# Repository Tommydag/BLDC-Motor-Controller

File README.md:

# BLDC-Motor-Controller
A BLDC Motor Controller for small electric vehicles

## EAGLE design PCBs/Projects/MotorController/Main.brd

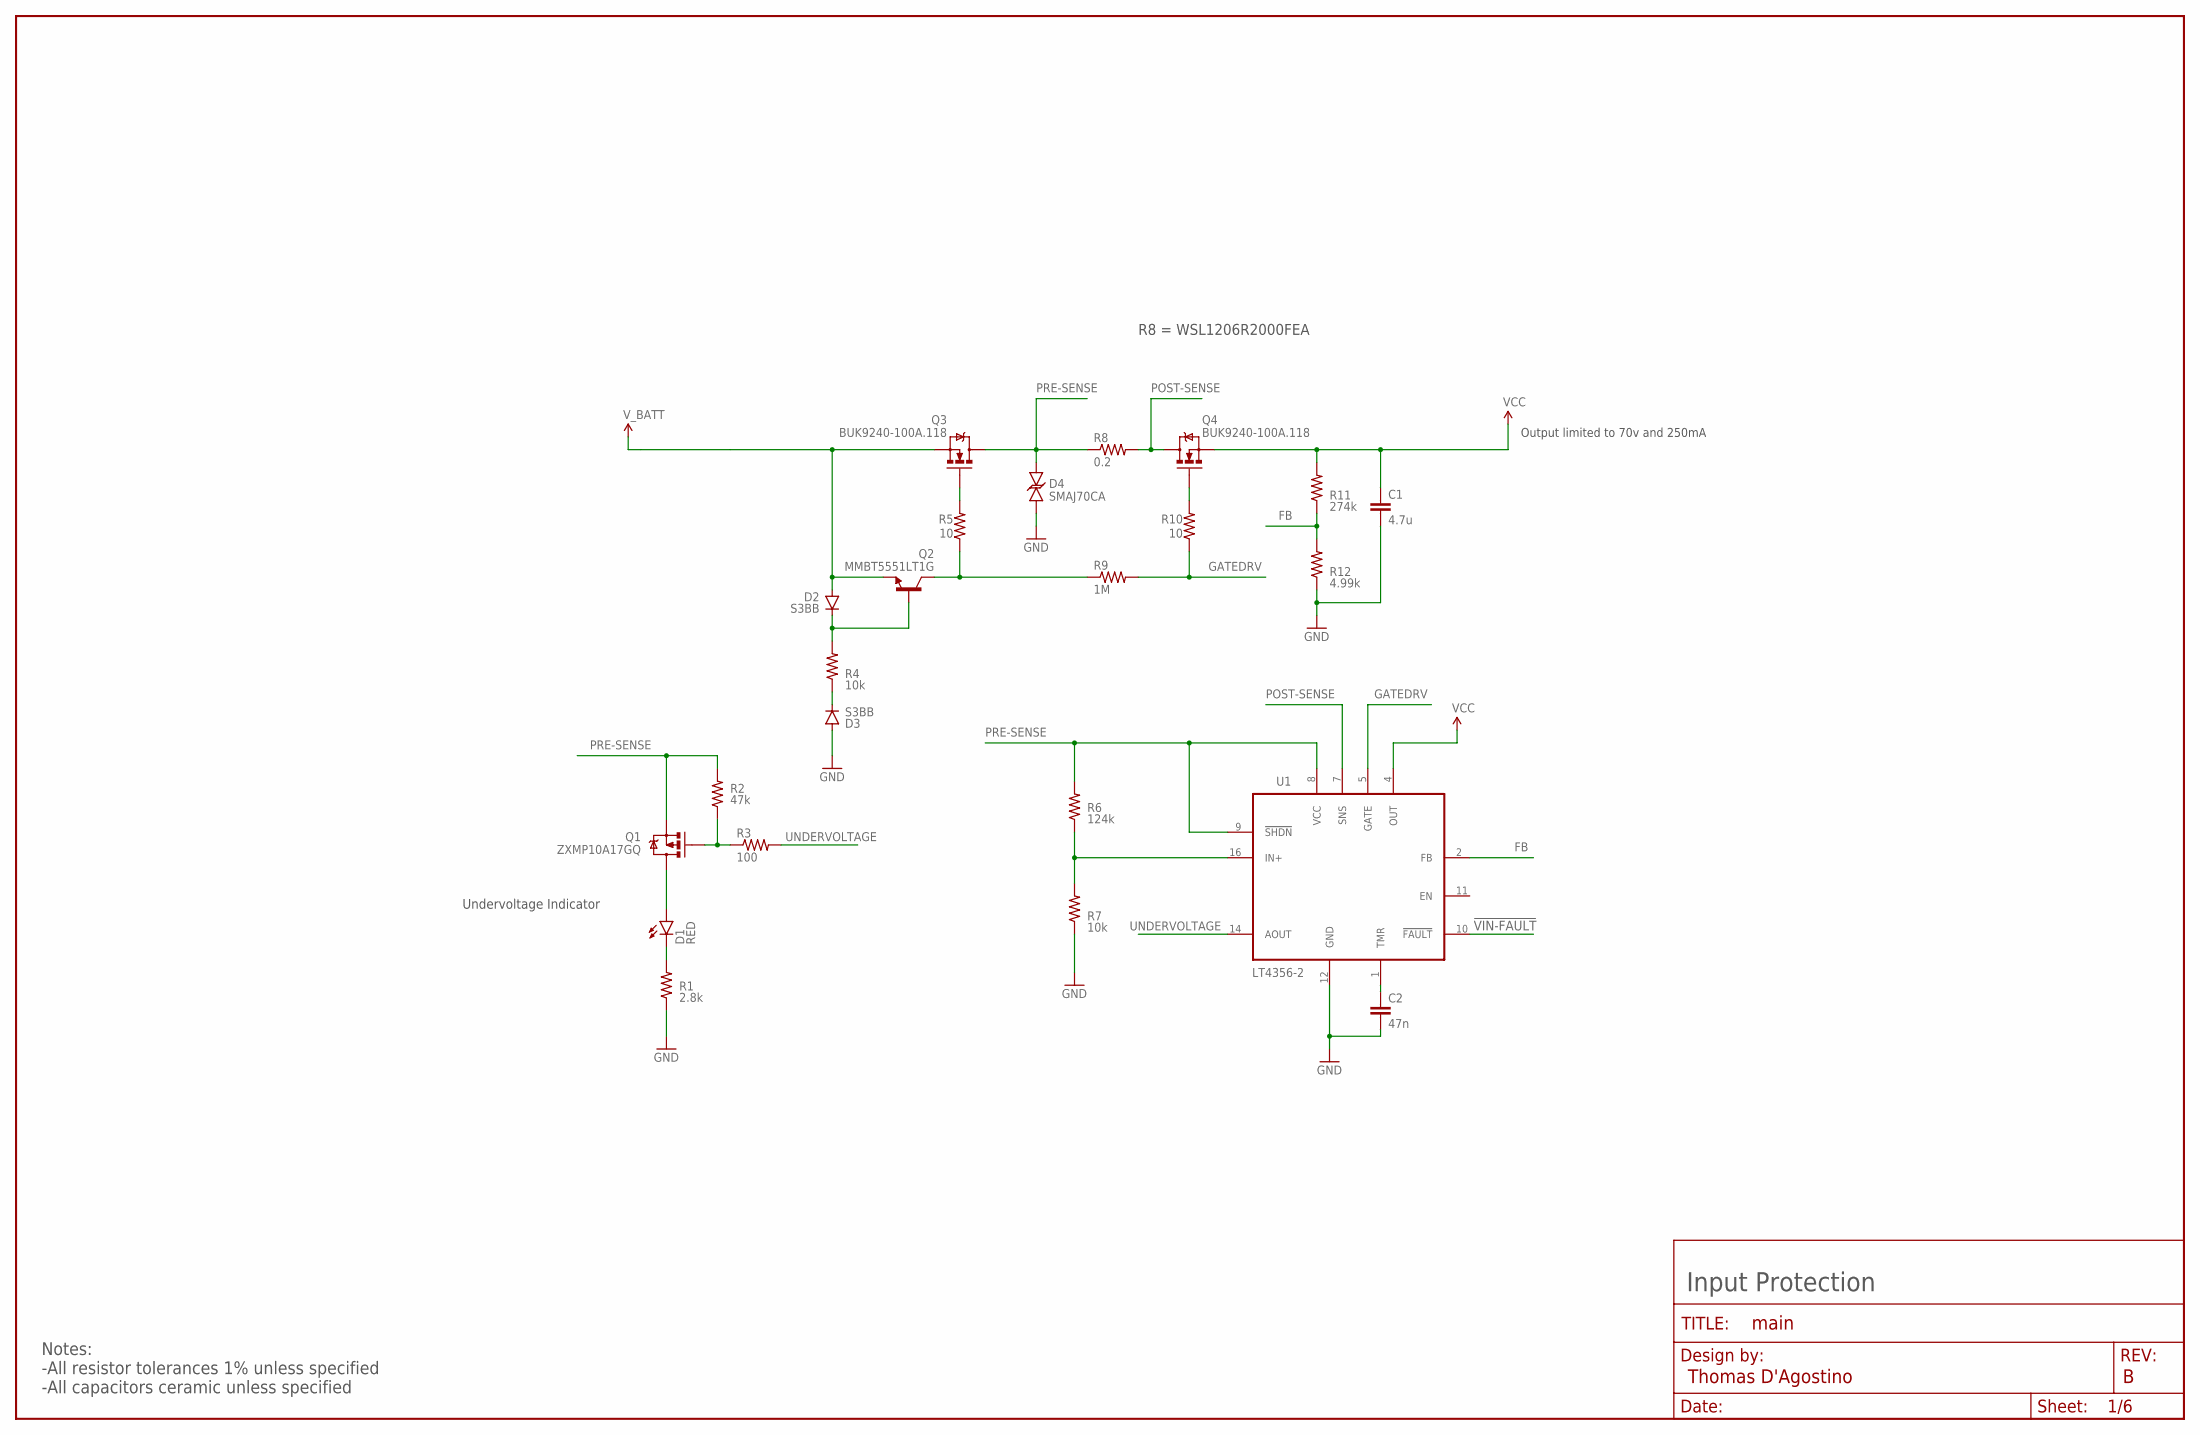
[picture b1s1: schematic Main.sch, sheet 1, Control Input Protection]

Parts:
C1: 4.7u; 1210
C2: 47n; 0805
D1: RED; LED-1206
D2, D3: S3BB; SMB-DIODE
D4: SMAJ70CA; SMA-DIODE-BI
FRAME1: FRAME-LEDGER; CREATIVE_COMMONS
Q1: ZXMP10A17GQ; SOT223
Q2: MMBT5551LT1G; SOT23-3
Q3, Q4: BUK9240-100A.118; DPAK
R1: 2.8k; 1206
R2: 47k; 0805
R3: 100; 0805
R4, R7: 10k; 0805
R5, R10: 10; 0805
R6: 124k; 0805
R8: 0.2; 1206
R9: 1M; 0805
R11: 274k; 0805
R12: 4.99k; 0805
U1: LT4356-2; SOIC-16

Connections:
!VIN-FAULT: U1.10 (!FAULT); also elsewhere on the board
FB: R11.1, R12.2, U1.2 (FB)
GATEDRV: R9.2, R10.1, U1.5 (GATE)
GND: C1.2, C2.2, D3.A, D4.A, R1.1, R7.1, R12.1, U1.12 (GND); also elsewhere on the board
unnamed: C2.1, U1.1 (TMR)
unnamed: D1.C, R1.2
unnamed: Q3.1 (G), R5.2
unnamed: D2.C, Q2.1 (B), R4.2
unnamed: Q4.1 (G), R10.2
unnamed: R6.1, R7.2, U1.16 (IN+)
unnamed: Q1.1 (G), R2.1, R3.1
unnamed: Q2.3 (C), R5.1, R9.1
unnamed: D1.A, Q1.2 (D), Q1.4 (D)
unnamed: D3.C, R4.1
POST-SENSE: Q4.4 (D), R8.2, U1.7 (SNS)
PRE-SENSE: D4.C, Q1.3 (S), Q3.4 (D), R2.2, R6.2, R8.1, U1.8 (VCC), U1.9 (!SHDN)
UNDERVOLTAGE: R3.2, U1.14 (AOUT)
VCC: C1.1, Q4.3 (S), R11.2, U1.4 (OUT); also elsewhere on the board
V_BATT: D2.A, Q2.2 (E), Q3.3 (S); also elsewhere on the board

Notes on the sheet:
Output limited to 70v and 250mA
Undervoltage Indicator
Input Protection
Notes: -All resistor tolerances 1% unless specified -All capacitors ceramic unless specified
R8 = WSL1206R2000FEA

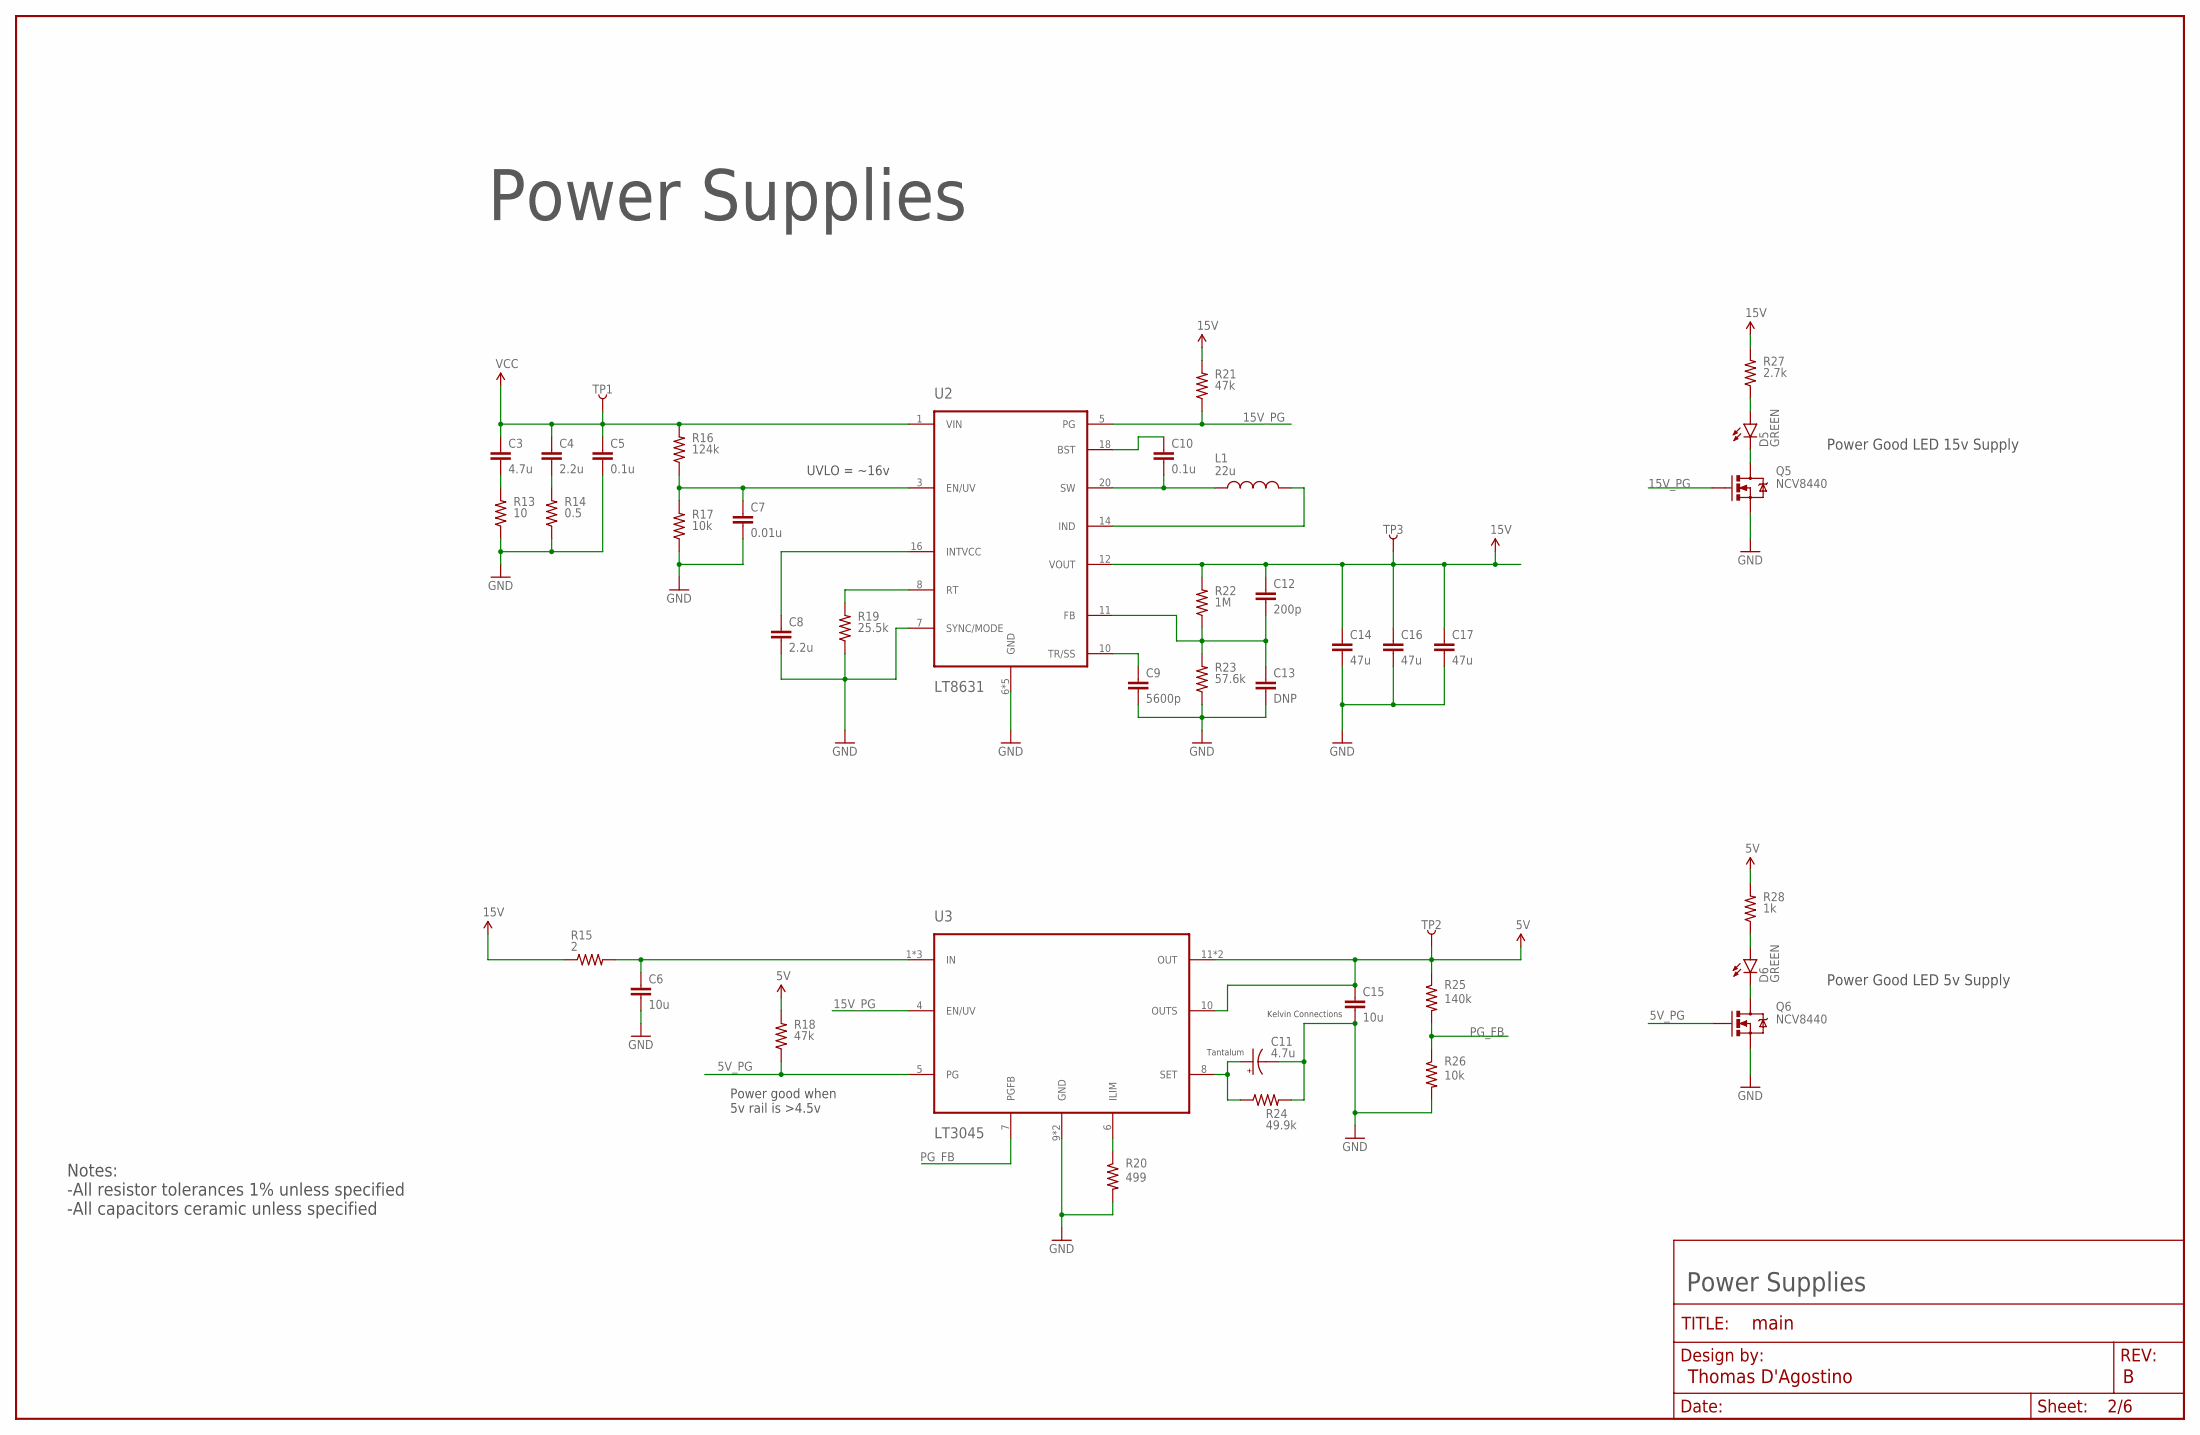
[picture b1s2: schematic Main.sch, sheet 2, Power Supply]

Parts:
C3: 4.7u; 1210
C4: 2.2u; 1210
C5, C10: 0.1u; 0805
C6, C15: 10u; 1210
C7: 0.01u; 0805
C8: 2.2u; 0805
C9: 5600p; 0805
C11: 4.7u; EIA3216
C12: 200p; 0805
C13: DNP; 0805
C14, C16, C17: 47u; 1210
D5, D6: GREEN; LED-1206
FRAME2: FRAME-LEDGER; CREATIVE_COMMONS
L1: 22u; IND_SMD_SRP7050TA
Q5, Q6: NCV8440; SOT223
R13: 10; 0805
R14: 0.5; 0805
R15: 2; 1206
R16: 124k; 0805
R17, R26: 10k; 0805
R18, R21: 47k; 0805
R19: 25.5k; 0805
R20: 499; 0805
R22: 1M; 0805
R23: 57.6k; 0805
R24: 49.9k; 0805
R25: 140k; 0805
R27: 2.7k; 0805
R28: 1k; 0805
TP1, TP2, TP3: TEST-POINTRCT-0C; TEST-POINT-MINI
U2: LT8631; TSSOP-20-FE
U3: LT3045; MSOP-12-EP

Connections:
5V: C15.1, R18.2, R25.1, R28.2, TP2.P$1, U3.10 (OUTS), U3.11 (OUT), U3.12 (OUT); also elsewhere on the board
5V_PG: Q6.1 (G), R18.1, U3.5 (PG)
5V_SET_CONNECTION: C11.A (+), R24.1, U3.8 (SET)
15V: C12.1, C14.1, C16.1, C17.1, R15.1, R21.2, R22.2, R27.2, TP3.P$1, U2.12 (VOUT); also elsewhere on the board
15V_PG: Q5.1 (G), R21.1, U2.5 (PG), U3.4 (EN/UV)
GND: C5.2, C6.2, C7.2, C8.2, C9.2, C11.C (-), C13.2, C14.2, C15.2, C16.2, C17.2, Q5.3 (S), Q6.3 (S), R13.1, R14.1, R17.1, R19.1, R20.2, R23.1, R24.2, R26.2, U2.6 (GND), U2.7 (SYNC/MODE), U2.9 (GND), U2.13 (GND), U2.15 (GND), U2.EXP (GND), U3.9 (GND), U3.EXP (GND); also elsewhere on the board
ILIMIT_5V: R20.1, U3.6 (ILIM)
unnamed: C10.2, L1.P$1 (1), U2.20 (SW)
unnamed: L1.P$2 (2), U2.14 (IND)
unnamed: C10.1, U2.18 (BST)
unnamed: C7.1, R16.1, R17.2, U2.3 (EN/UV)
unnamed: C8.1, U2.16 (INTVCC)
unnamed: R19.2, U2.8 (RT)
unnamed: C9.1, U2.10 (TR/SS)
unnamed: C12.2, C13.1, R22.1, R23.2, U2.11 (FB)
unnamed: C6.1, R15.2, U3.1 (IN), U3.2 (IN), U3.3 (IN)
unnamed: C3.2, R13.2
unnamed: C4.2, R14.2
unnamed: D5.C, Q5.2 (D), Q5.4 (D)
unnamed: D5.A, R27.1
unnamed: D6.A, R28.1
unnamed: D6.C, Q6.2 (D), Q6.4 (D)
PG_FB: R25.2, R26.1, U3.7 (PGFB)
VCC: C3.1, C4.1, C5.1, R16.2, TP1.P$1, U2.1 (VIN); also elsewhere on the board

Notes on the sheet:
Power Supplies
Notes: -All resistor tolerances 1% unless specified -All capacitors ceramic unless specified
UVLO = ~16v
Kelvin Connections
Power good when 5v rail is >4.5v
Tantalum
Power Good LED 15v Supply
Power Good LED 5v Supply

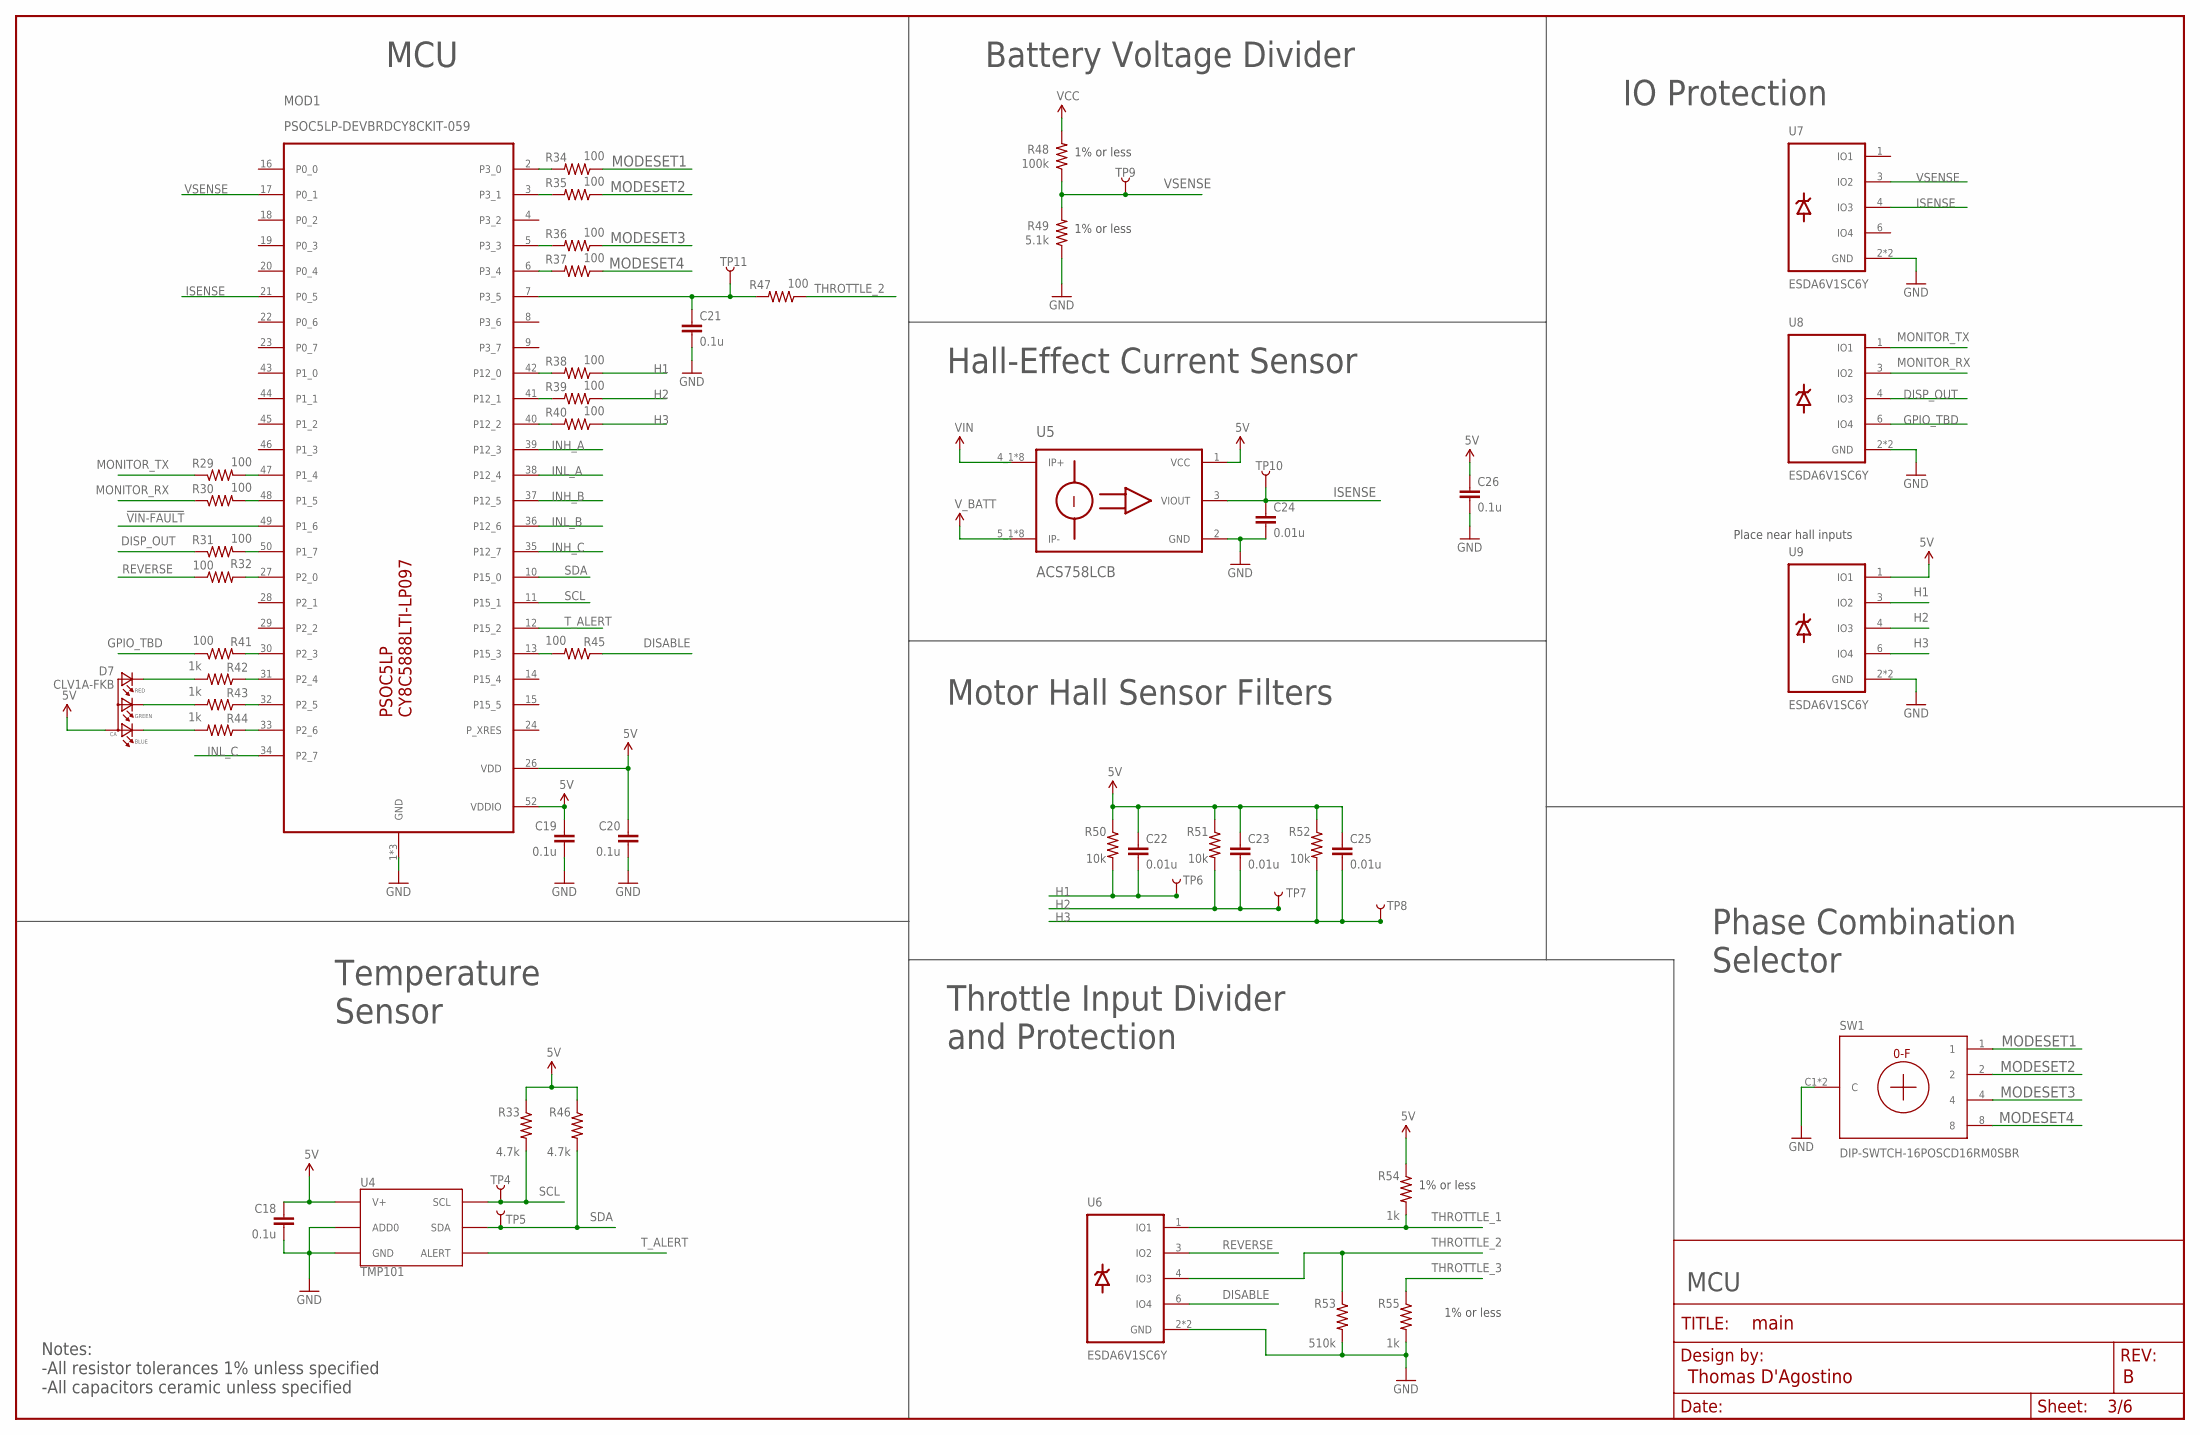
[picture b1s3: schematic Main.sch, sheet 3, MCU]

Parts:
C18, C19, C20, C21, C26: 0.1u; 0805
C22, C23, C24, C25: 0.01u; 0805
D7: CLV1A-FKB; P-LCC-4-3
FRAME3: FRAME-LEDGER; CREATIVE_COMMONS
MOD1: PSOC5LP-DEVBRDCY8CKIT-059; CYKIT059
R29, R30, R31, R32, R34, R35, R36, R37, R38, R39, R40, R41, R45, R47: 100; 0805
R33, R46: 4.7k; 0805
R42, R43, R44, R54, R55: 1k; 0805
R48: 100k; 1206
R49: 5.1k; 1206
R50, R51, R52: 10k; 0805
R53: 510k; 0805
SW1: DIP-SWTCH-16POSCD16RM0SBR; DIP-8MM
TP4, TP5, TP6, TP7, TP8, TP9, TP10, TP11: TEST-POINTRCT-0C; TEST-POINT-MINI
U4: TMP101; SOT23-6
U5: ACS758LCB; CB5PIN
U6, U7, U8, U9: ESDA6V1SC6Y; SOT23-6

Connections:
5V: C18.1, C19.1, C20.1, C22.1, C23.1, C25.1, C26.1, D7.2 (ANODE), MOD1.26 (VDD), MOD1.52 (VDDIO), R33.1, R46.1, R50.1, R51.1, R52.1, R54.1, U4.4 (V+), U5.1 (VCC), U9.1 (IO1); also elsewhere on the board
!VIN-FAULT: MOD1.49 (P1_6); also elsewhere on the board
DISABLE: R45.1, U6.6 (IO4); also elsewhere on the board
DISP_OUT: R31.1, U8.6 (IO4); also elsewhere on the board
GND: C18.2, C19.2, C20.2, C21.2, C24.2, C26.2, MOD1.1 (GND), MOD1.25 (GND), MOD1.51 (GND), R49.1, R53.2, R55.2, SW1.C1 (C), SW1.C2 (C), U4.2 (GND), U4.5 (ADD0), U5.2 (GND), U6.2 (GND), U6.5 (GND), U7.2 (GND), U7.5 (GND), U8.2 (GND), U8.5 (GND), U9.2 (GND), U9.5 (GND); also elsewhere on the board
GPIO_TBD: R41.1, U8.4 (IO3); also elsewhere on the board
H1: C22.2, R38.1, R50.2, TP6.P$1, U9.3 (IO2); also elsewhere on the board
H2: C23.2, R39.1, R51.2, TP7.P$1, U9.4 (IO3); also elsewhere on the board
H3: C25.2, R40.1, R52.2, TP8.P$1, U9.6 (IO4); also elsewhere on the board
INH_A: MOD1.39 (P12_3); also elsewhere on the board
INH_B: MOD1.37 (P12_5); also elsewhere on the board
INH_C: MOD1.35 (P12_7); also elsewhere on the board
INL_A: MOD1.38 (P12_4); also elsewhere on the board
INL_B: MOD1.36 (P12_6); also elsewhere on the board
INL_C: MOD1.34 (P2_7); also elsewhere on the board
ISENSE: C24.1, MOD1.21 (P0_5), TP10.P$1, U5.3 (VIOUT), U7.4 (IO3)
MODESET1: R34.1, SW1.1
MODESET2: R35.1, SW1.2
MODESET3: R36.1, SW1.4
MODESET4: R37.1, SW1.8
MONITOR_RX: R30.1, U8.1 (IO1); also elsewhere on the board
MONITOR_TX: R29.1, U8.3 (IO2); also elsewhere on the board
unnamed: MOD1.42 (P12_0), R38.2
unnamed: MOD1.13 (P15_3), R45.2
unnamed: MOD1.5 (P3_3), R36.2
unnamed: MOD1.33 (P2_6), R44.1
unnamed: MOD1.32 (P2_5), R43.1
unnamed: MOD1.31 (P2_4), R42.1
unnamed: D7.3 (BLUE), R44.2
unnamed: D7.4 (GREEN), R43.2
unnamed: D7.1 (RED), R42.2
unnamed: C21.1, MOD1.7 (P3_5), R47.2, TP11.P$1
unnamed: MOD1.50 (P1_7), R31.2
unnamed: MOD1.30 (P2_3), R41.2
unnamed: MOD1.47 (P1_4), R29.2
unnamed: MOD1.48 (P1_5), R30.2
unnamed: MOD1.41 (P12_1), R39.2
unnamed: MOD1.40 (P12_2), R40.2
unnamed: MOD1.27 (P2_0), R32.2
unnamed: MOD1.3 (P3_1), R35.2
unnamed: MOD1.2 (P3_0), R34.2
unnamed: MOD1.6 (P3_4), R37.2
REVERSE: R32.1, U6.3 (IO2); also elsewhere on the board
SCL: MOD1.11 (P15_1), R33.2, TP4.P$1, U4.1 (SCL)
SDA: MOD1.10 (P15_0), R46.2, TP5.P$1, U4.6 (SDA)
THROTTLE_1: R54.2, U6.1 (IO1); also elsewhere on the board
THROTTLE_2: R47.1, R53.1, U6.4 (IO3); also elsewhere on the board
THROTTLE_3: R55.1; also elsewhere on the board
T_ALERT: MOD1.12 (P15_2), U4.3 (ALERT)
VCC: R48.2; also elsewhere on the board
VIN: U5.4_1 (IP+), U5.4_2 (IP+), U5.4_3 (IP+), U5.4_4 (IP+), U5.4_5 (IP+), U5.4_6 (IP+), U5.4_7 (IP+), U5.4_8 (IP+); also elsewhere on the board
VSENSE: MOD1.17 (P0_1), R48.1, R49.2, TP9.P$1, U7.3 (IO2)
V_BATT: U5.5_1 (IP-), U5.5_2 (IP-), U5.5_3 (IP-), U5.5_4 (IP-), U5.5_5 (IP-), U5.5_6 (IP-), U5.5_7 (IP-), U5.5_8 (IP-); also elsewhere on the board

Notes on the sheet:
Place near hall inputs
1% or less
MCU
Temperature Sensor
Battery Voltage Divider
Hall-Effect Current Sensor
Motor Hall Sensor Filters
Throttle Input Divider and Protection
IO Protection
Notes: -All resistor tolerances 1% unless specified -All capacitors ceramic unless specified
Phase Combination Selector

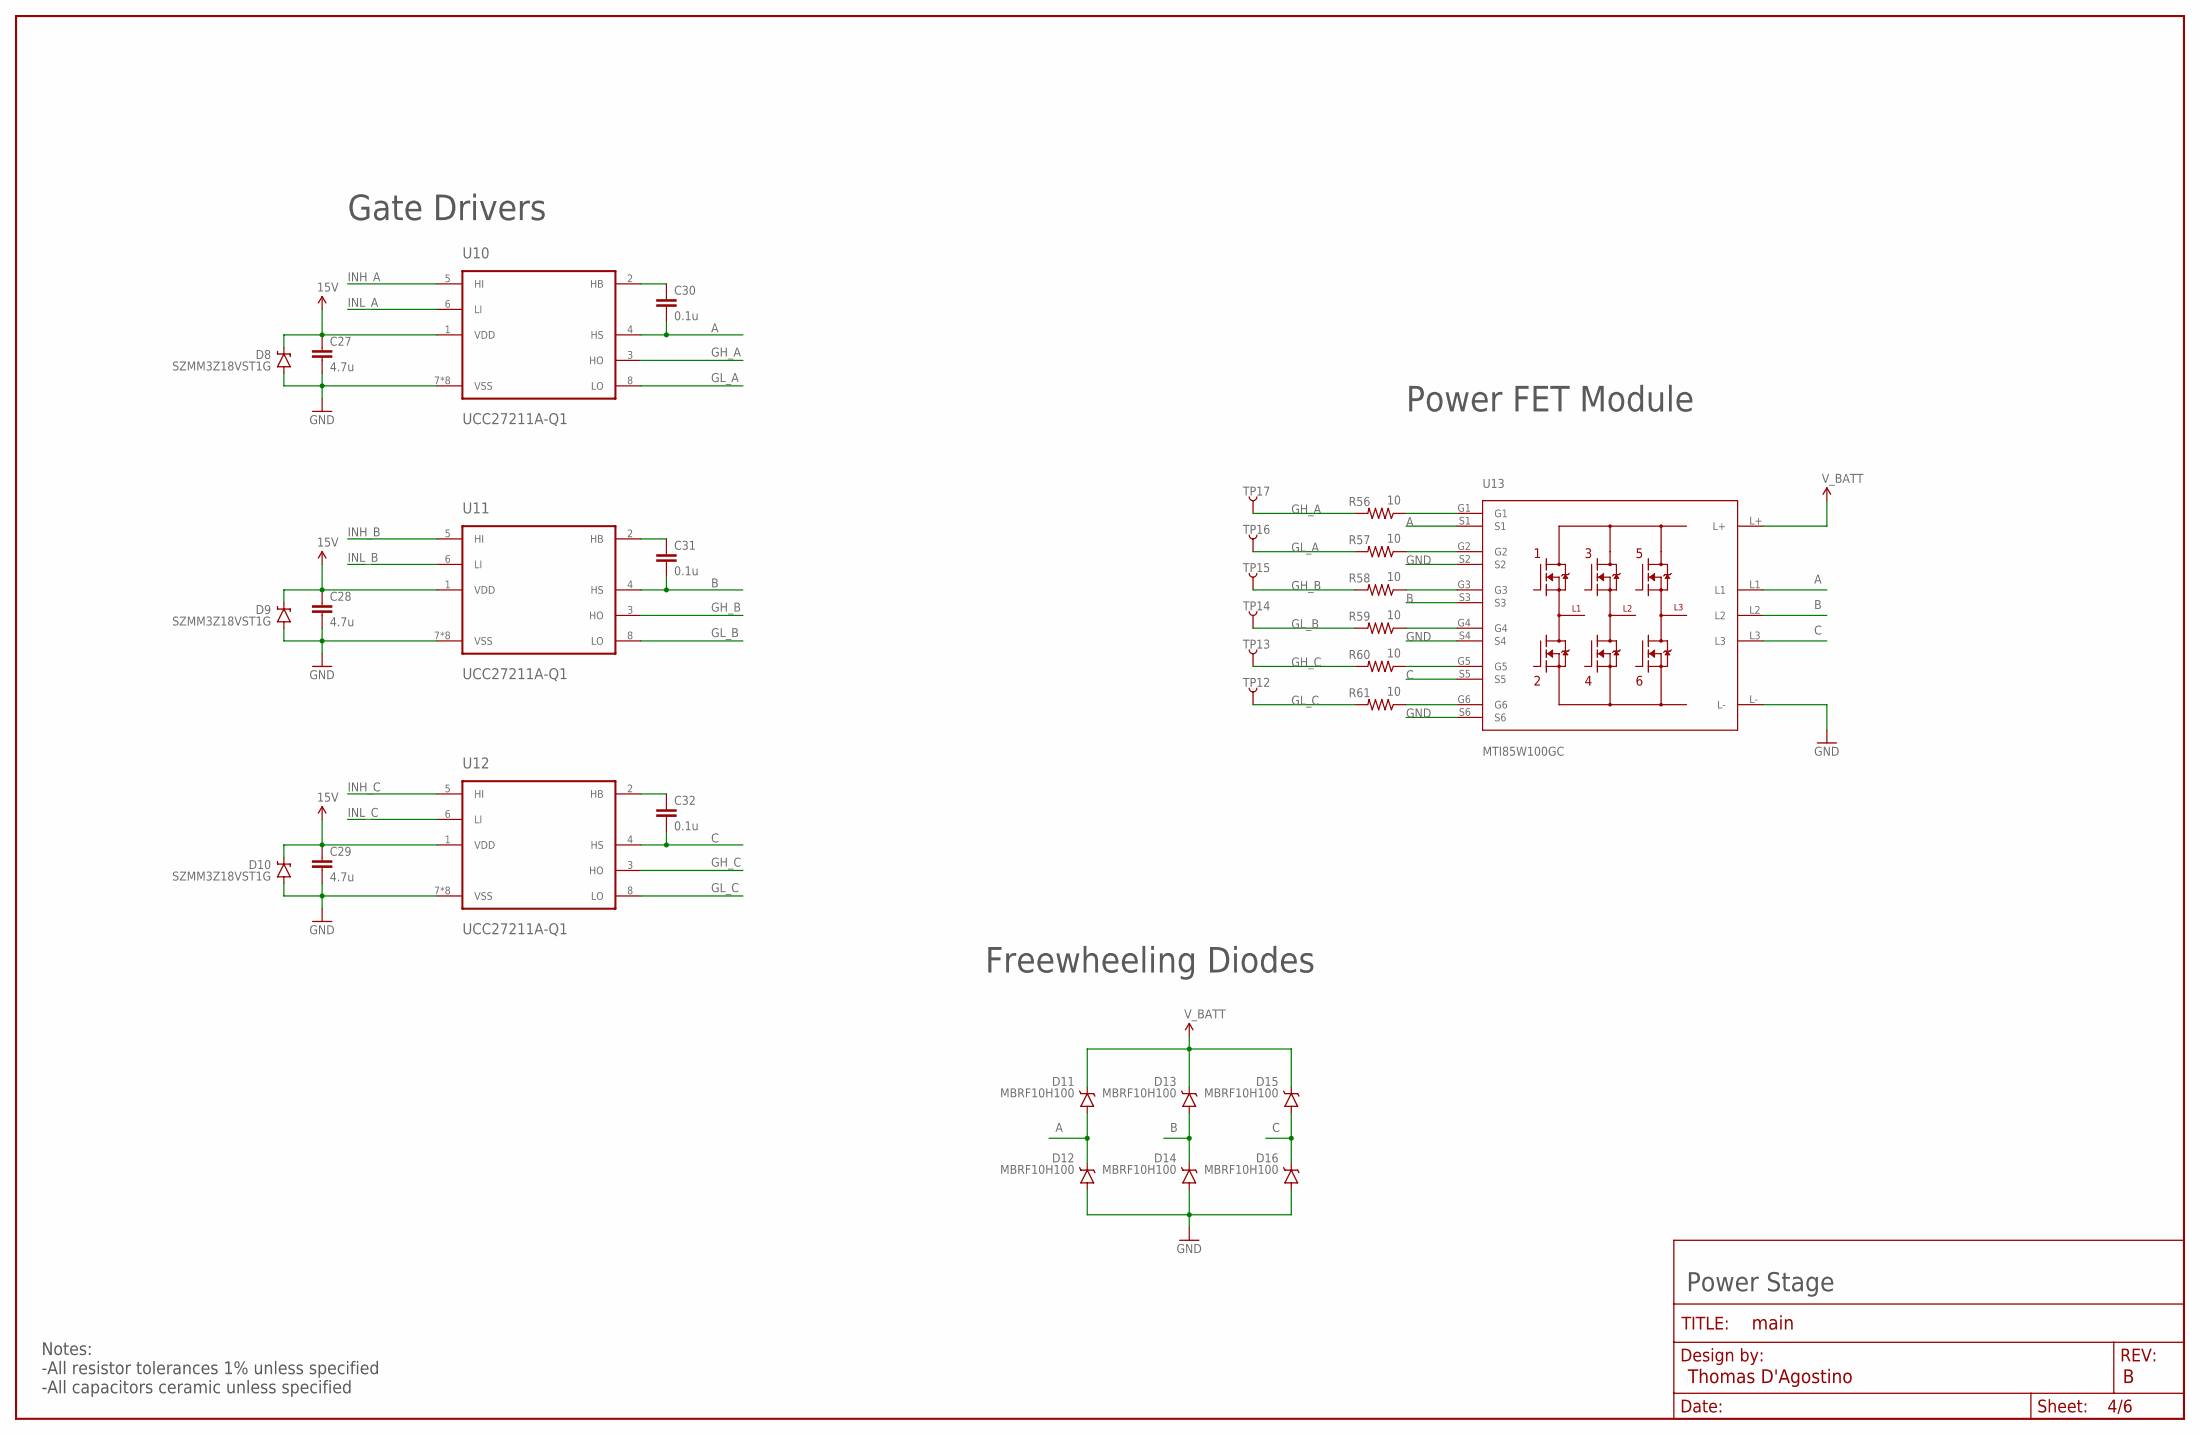
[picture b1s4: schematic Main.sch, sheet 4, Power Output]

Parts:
C27, C28, C29: 4.7u; 1210
C30, C31, C32: 0.1u; 0805
D8, D9, D10: SZMM3Z18VST1G; SOD-323
D11, D12, D13, D14, D15, D16: MBRF10H100; TO220V_2
FRAME4: FRAME-LEDGER; CREATIVE_COMMONS
R56, R57, R58, R59, R60, R61: 10; 0805
TP12, TP13, TP14, TP15, TP16, TP17: TEST-POINTRCT-0C; TEST-POINT-MINI
U10, U11, U12: UCC27211A-Q1; SOIC-8-EP
U13: MTI85W100GC; ISOPLUS-DIL

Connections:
15V: C27.1, C28.1, C29.1, D8.C, D9.C, D10.C, U10.1 (VDD), U11.1 (VDD), U12.1 (VDD); also elsewhere on the board
A: C30.2, D11.2 (A), D12.1 (C), U10.4 (HS), U13.L1, U13.S1; also elsewhere on the board
B: C31.2, D13.2 (A), D14.1 (C), U11.4 (HS), U13.L2, U13.S3; also elsewhere on the board
C: C32.2, D15.2 (A), D16.1 (C), U12.4 (HS), U13.L3, U13.S5; also elsewhere on the board
GH_A: R56.2, TP17.P$1, U10.3 (HO)
GH_B: R58.2, TP15.P$1, U11.3 (HO)
GH_C: R60.2, TP13.P$1, U12.3 (HO)
GL_A: R57.2, TP16.P$1, U10.8 (LO)
GL_B: R59.2, TP14.P$1, U11.8 (LO)
GL_C: R61.2, TP12.P$1, U12.8 (LO)
GND: C27.2, C28.2, C29.2, D8.A, D9.A, D10.A, D12.2 (A), D14.2 (A), D16.2 (A), U10.7 (VSS), U10.EP1 (VSS), U10.EP2 (VSS), U10.EP3 (VSS), U10.EP4 (VSS), U10.EP5 (VSS), U10.EP6 (VSS), U10.EXP (VSS), U11.7 (VSS), U11.EP1 (VSS), U11.EP2 (VSS), U11.EP3 (VSS), U11.EP4 (VSS), U11.EP5 (VSS), U11.EP6 (VSS), U11.EXP (VSS), U12.7 (VSS), U12.EP1 (VSS), U12.EP2 (VSS), U12.EP3 (VSS), U12.EP4 (VSS), U12.EP5 (VSS), U12.EP6 (VSS), U12.EXP (VSS), U13.L-, U13.S2, U13.S4, U13.S6; also elsewhere on the board
INH_A: U10.5 (HI); also elsewhere on the board
INH_B: U11.5 (HI); also elsewhere on the board
INH_C: U12.5 (HI); also elsewhere on the board
INL_A: U10.6 (LI); also elsewhere on the board
INL_B: U11.6 (LI); also elsewhere on the board
INL_C: U12.6 (LI); also elsewhere on the board
unnamed: C30.1, U10.2 (HB)
unnamed: C31.1, U11.2 (HB)
unnamed: C32.1, U12.2 (HB)
unnamed: R58.1, U13.G3
unnamed: R56.1, U13.G1
unnamed: R57.1, U13.G2
unnamed: R59.1, U13.G4
unnamed: R60.1, U13.G5
unnamed: R61.1, U13.G6
V_BATT: D11.1 (C), D13.1 (C), D15.1 (C), U13.L+; also elsewhere on the board

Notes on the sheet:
Freewheeling Diodes
Power FET Module
Power Stage
Notes: -All resistor tolerances 1% unless specified -All capacitors ceramic unless specified
Gate Drivers

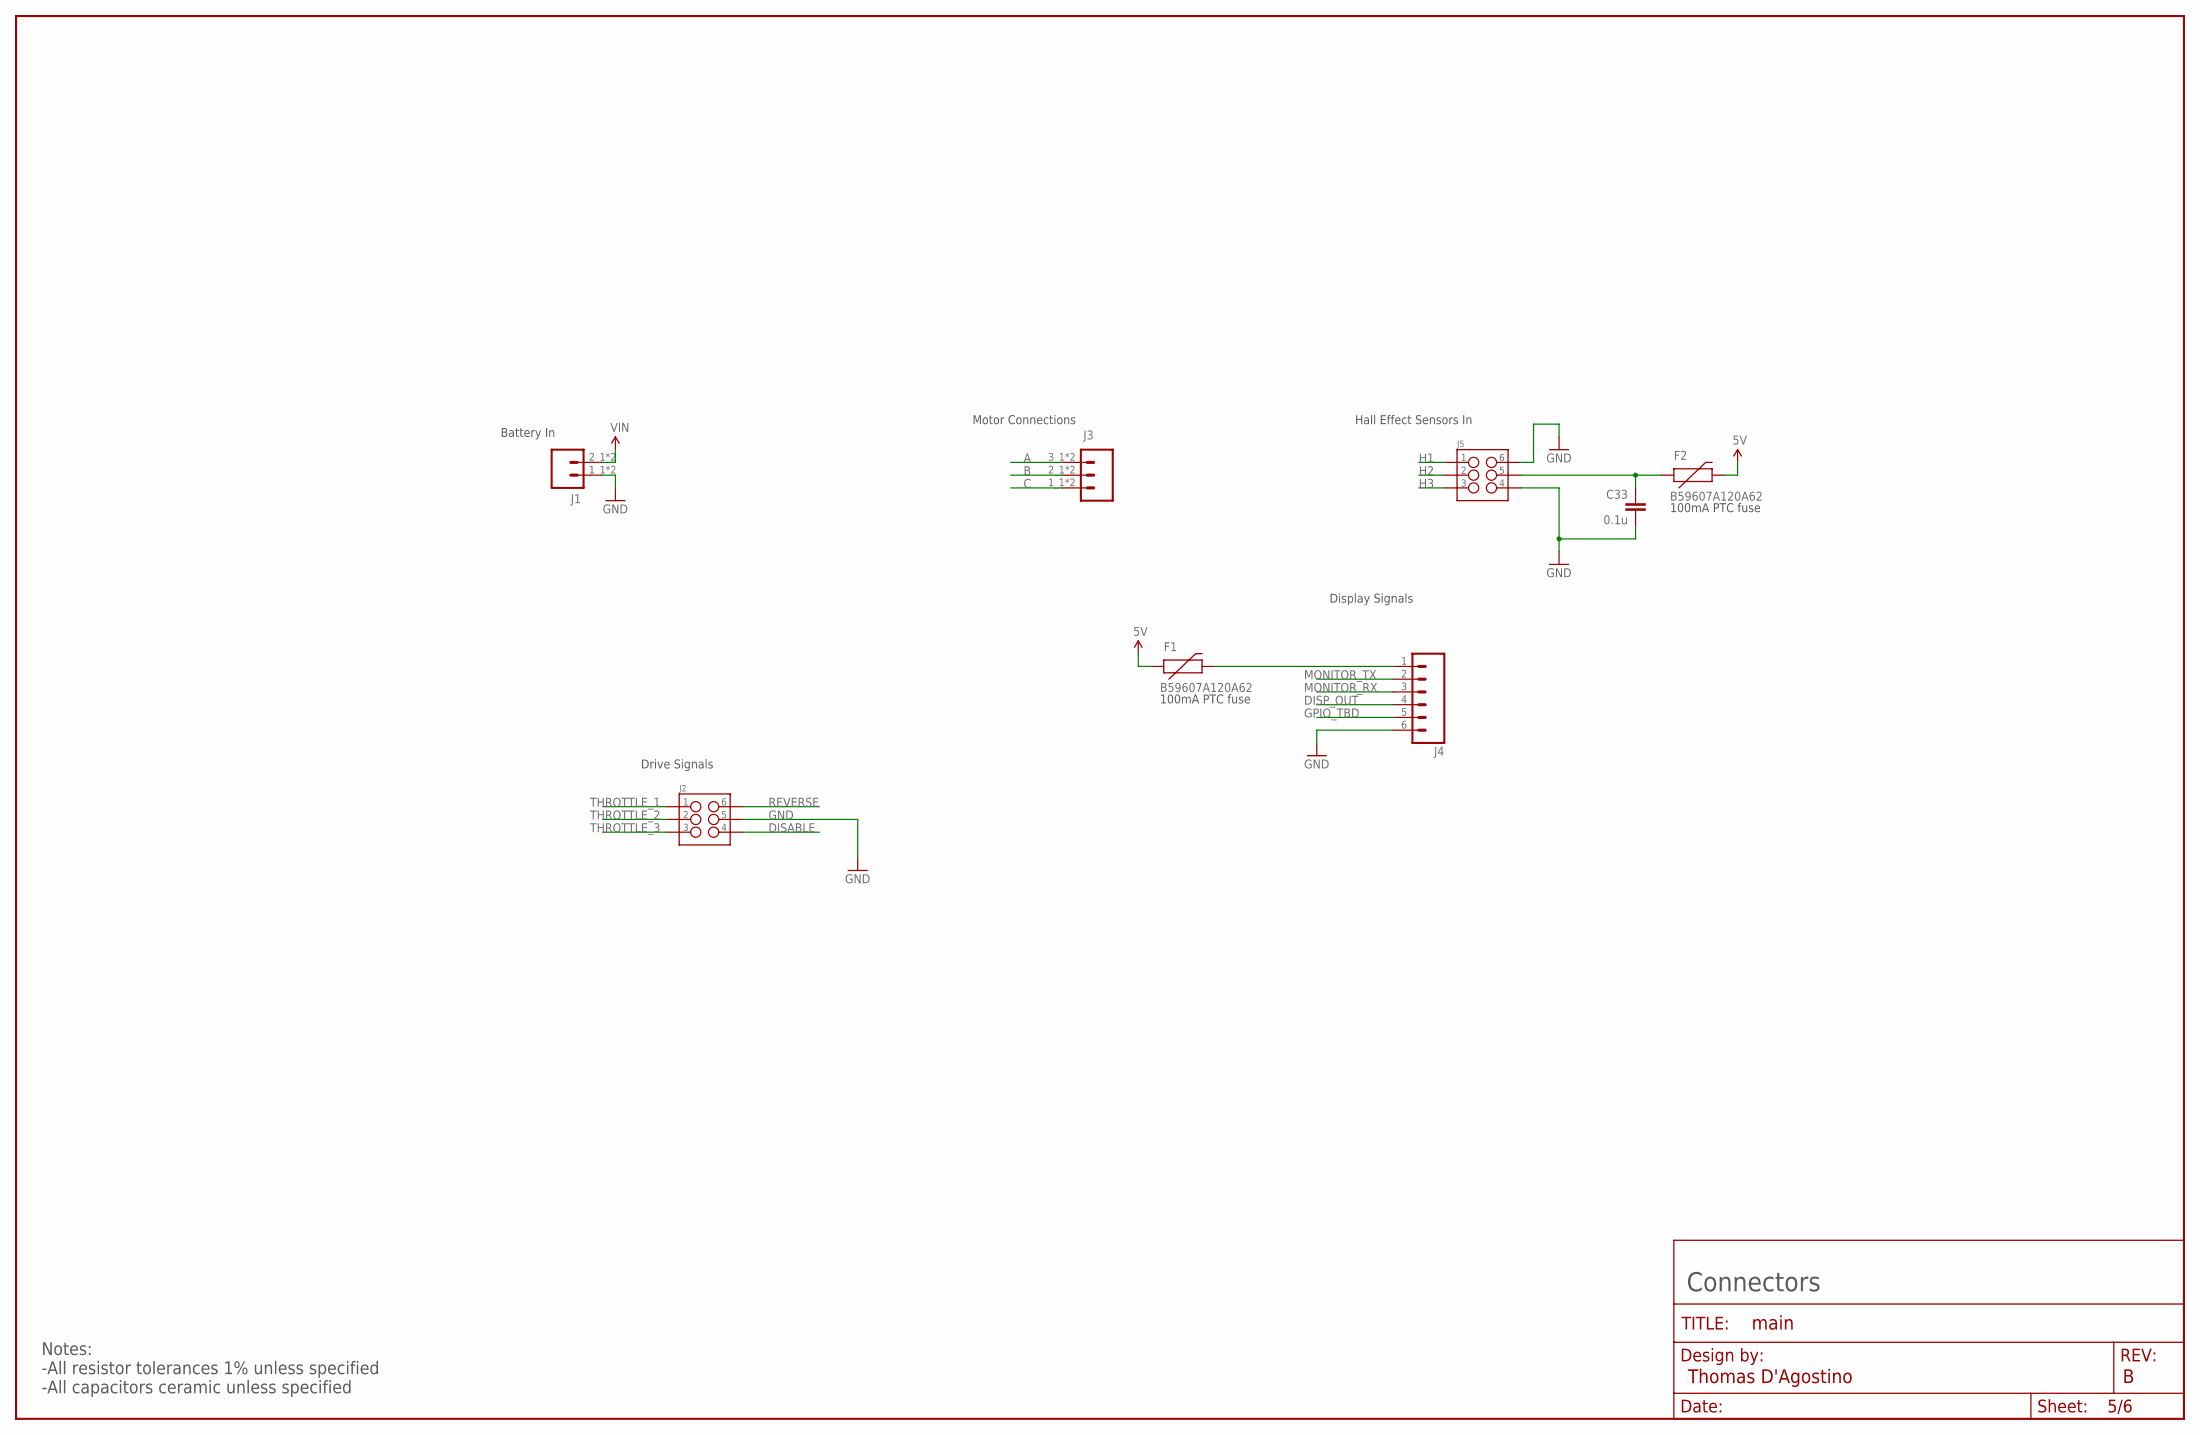
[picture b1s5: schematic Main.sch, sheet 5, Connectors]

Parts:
C33: 0.1u; 0805
F1, F2: B59607A120A62; 1210
FRAME5: FRAME-LEDGER; CREATIVE_COMMONS
J1: M02MINIFIT-SR; MINIFIT_SR
J2, J5: M03X2MINIFIT_JR; 2X03_MINIFIT_JR
J3: M03MINIFIT-SR3; MINIFIT-SRX3
J4: M06SILK_FEMALE_PTH; 1X06

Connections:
5V: F1.1, F2.2; also elsewhere on the board
A: J3.3_1 (3), J3.3_2 (3); also elsewhere on the board
B: J3.2_1 (2), J3.2_2 (2); also elsewhere on the board
C: J3.1_1 (1), J3.1_2 (1); also elsewhere on the board
DISABLE: J2.4; also elsewhere on the board
DISP_OUT: J4.4; also elsewhere on the board
GND: C33.2, J1.1_1 (1), J1.1_2 (1), J2.5, J4.6, J5.4, J5.6; also elsewhere on the board
GPIO_TBD: J4.5; also elsewhere on the board
H1: J5.1; also elsewhere on the board
H2: J5.2; also elsewhere on the board
H3: J5.3; also elsewhere on the board
MONITOR_RX: J4.3; also elsewhere on the board
MONITOR_TX: J4.2; also elsewhere on the board
unnamed: F1.2, J4.1
unnamed: C33.1, F2.1, J5.5
REVERSE: J2.6; also elsewhere on the board
THROTTLE_1: J2.1; also elsewhere on the board
THROTTLE_2: J2.2; also elsewhere on the board
THROTTLE_3: J2.3; also elsewhere on the board
VIN: J1.2_1 (2), J1.2_2 (2); also elsewhere on the board

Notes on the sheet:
Hall Effect Sensors In
Battery In
Drive Signals
Motor Connections
Display Signals
Connectors
Notes: -All resistor tolerances 1% unless specified -All capacitors ceramic unless specified
100mA PTC fuse

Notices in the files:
parts and their libraries:
SparkFun-Capacitors: Licensing: Creative Commons ShareAlike 4.0 International - https://creativecommons.org/licenses/by-sa/4.0
